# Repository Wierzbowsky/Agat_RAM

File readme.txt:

128kb RAM expansion for Agat computer v1.0. Created in 2016 by Wierzbowsky [RBSC].

Commercial usage is not allowed without the author's approval.

Contact: wierzbowsky@rbsc.su 

For more information see this forum's thread (in Russian): http://forum.agatcomp.ru//viewtopic.php?id=13

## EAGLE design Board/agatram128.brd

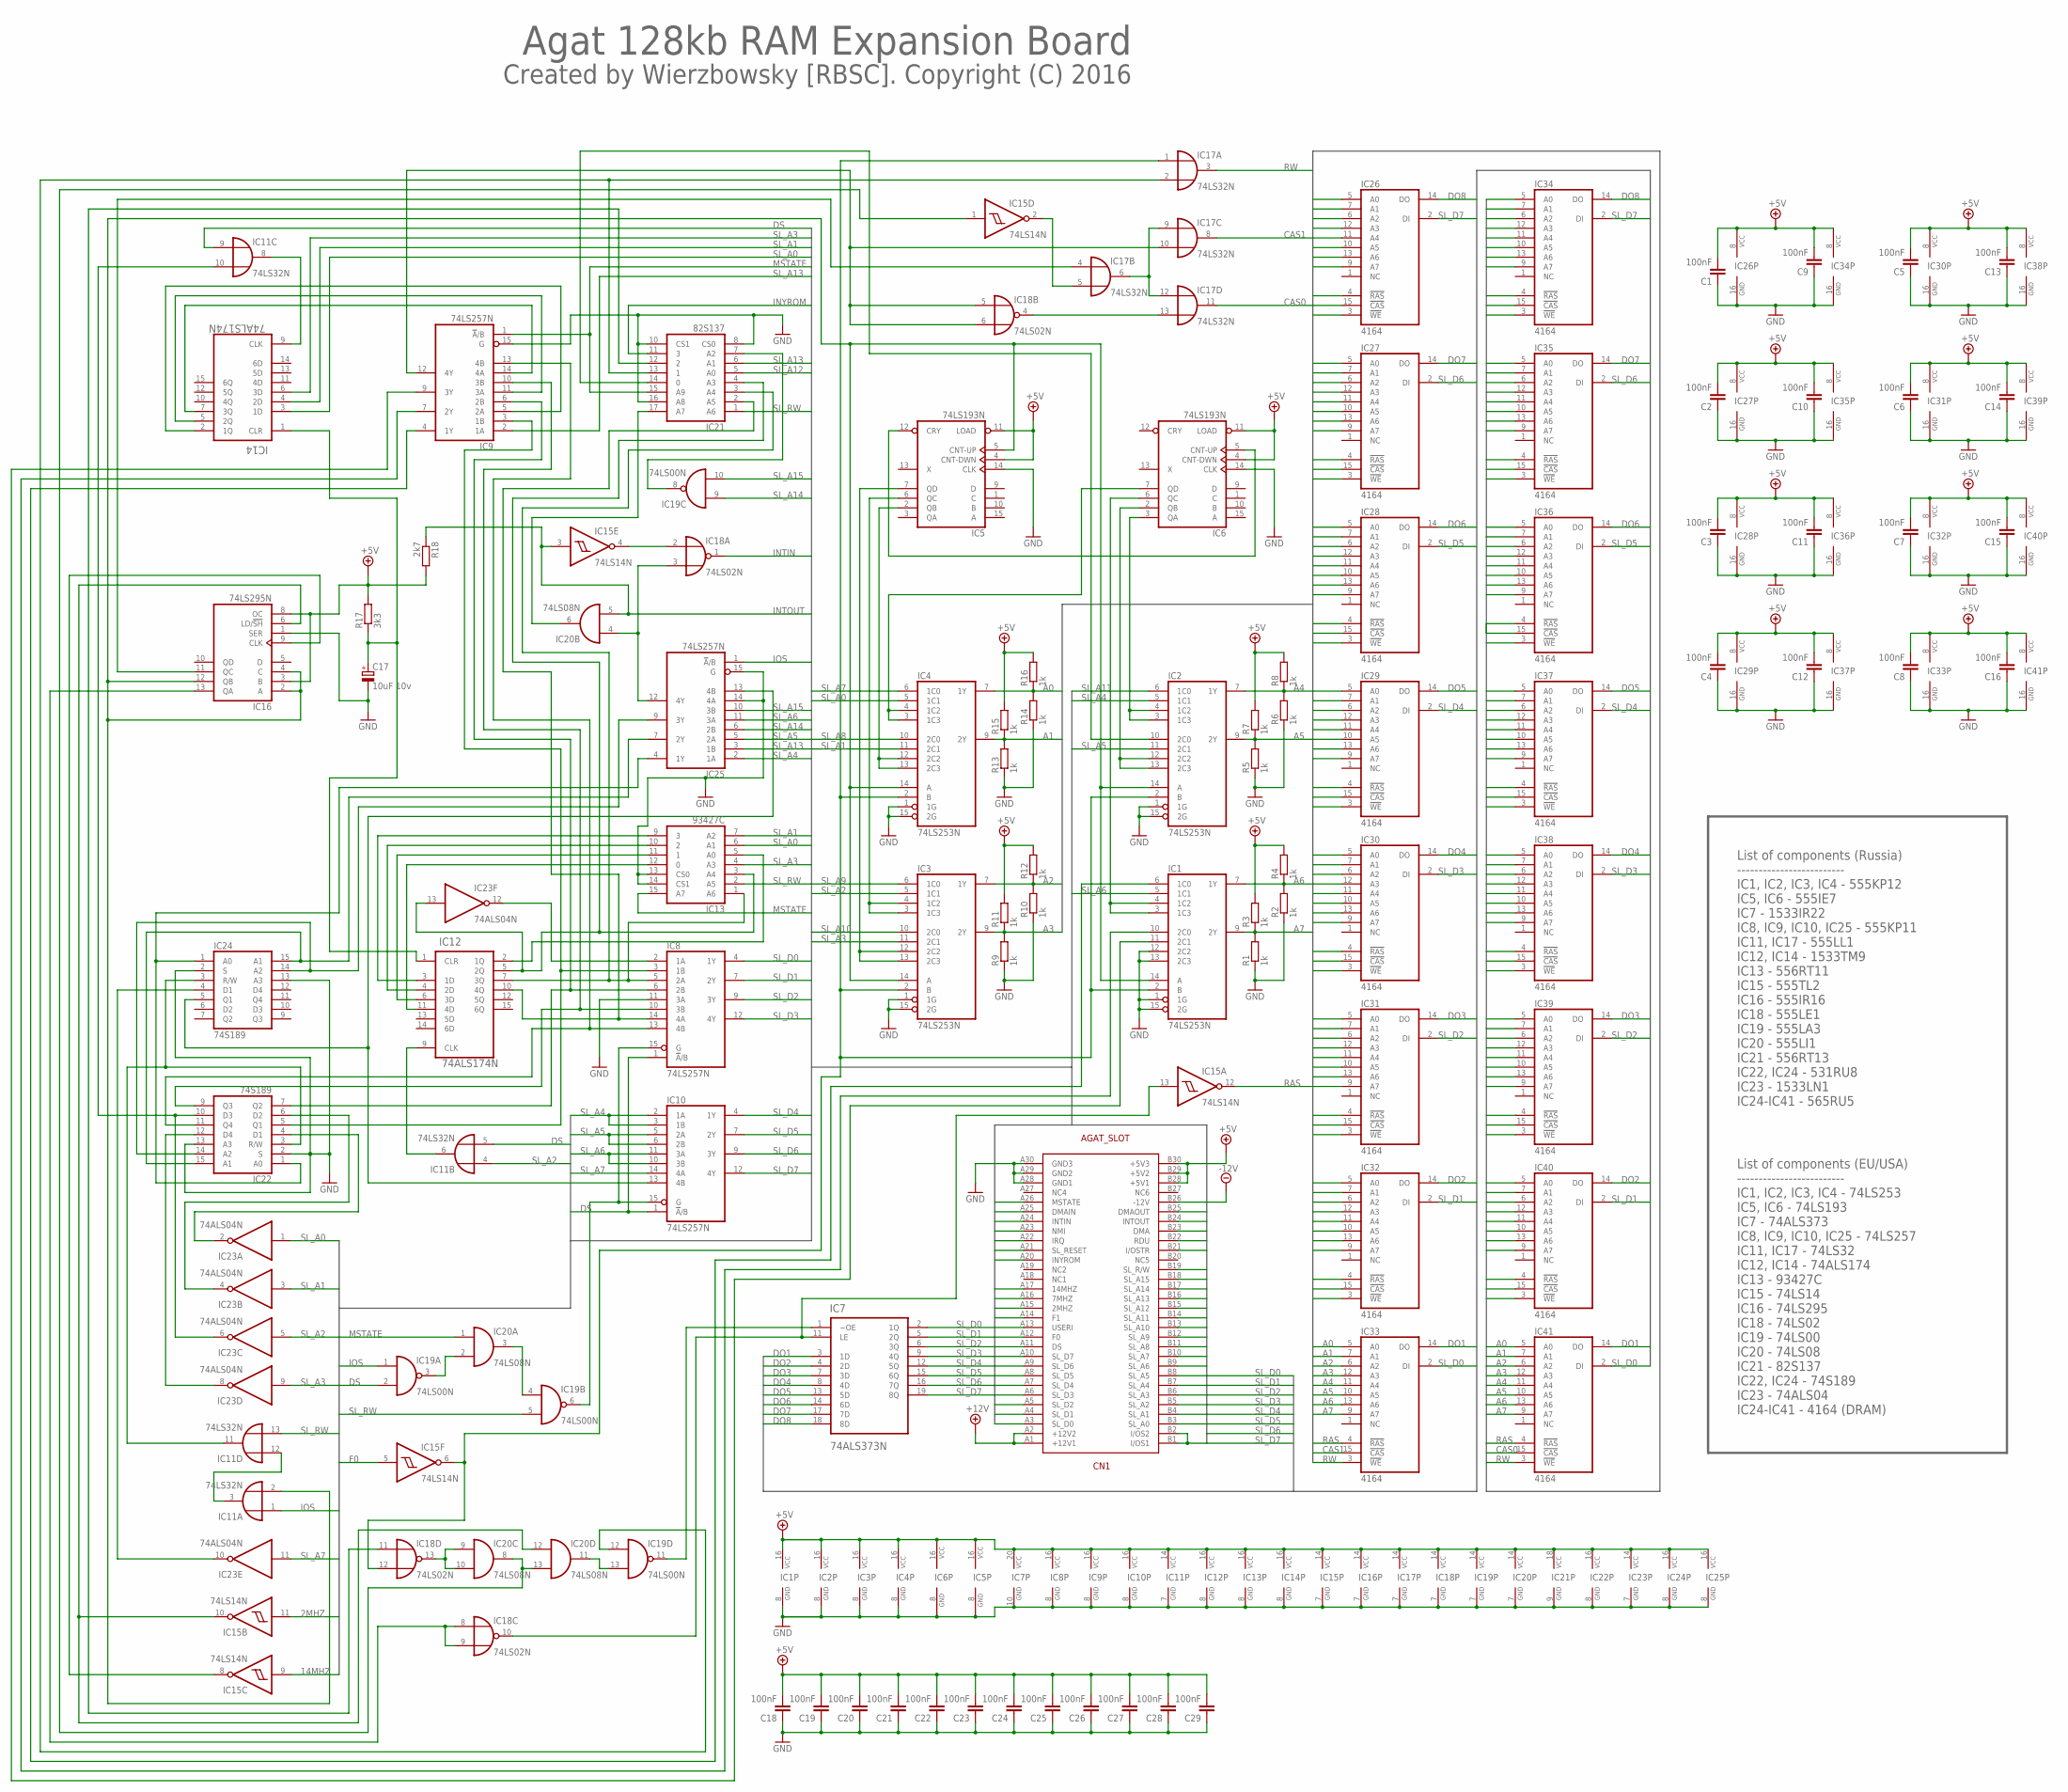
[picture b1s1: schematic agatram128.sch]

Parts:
C1, C2, C3, C4, C5, C6, C7, C8, C9, C10, C11, C12, C13, C14, C15, C16, C18, C19, C20, C21, C22, C23, C24, C25, C26, C27, C28, C29: 100nF; C050-025X075
C17: 10uF 10v; E15-5
CN1: AGAT_SLOT; AGAT_CONP
IC1, IC2, IC3, IC4: 74LS253N; DIL16
IC5, IC6: 74LS193N; DIL16
IC7: 74ALS373N; DIL20
IC8, IC9, IC10, IC25: 74LS257N; DIL16
IC11, IC17: 74LS32N; DIL14
IC12, IC14: 74ALS174N; DIL16
IC13: 93427C; DIL16
IC15: 74LS14N; DIL14
IC16: 74LS295N; DIL14
IC18: 74LS02N; DIL14
IC19: 74LS00N; DIL14
IC20: 74LS08N; DIL14
IC21: 82S137; DIL18
IC22, IC24: 74S189; DIL16
IC23: 74ALS04N; DIL14
IC26, IC27, IC28, IC29, IC30, IC31, IC32, IC33, IC34, IC35, IC36, IC37, IC38, IC39, IC40, IC41: 4164; DIL16
R1, R2, R3, R4, R5, R6, R7, R8, R9, R10, R11, R12, R13, R14, R15, R16: 1k; 0204/7
R17: 3k3; 0204/7
R18: 2k7; 0204/7

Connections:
2MHZ: CN1.A15 (2MHZ), IC15.11 (I)
7MHZ: CN1.A16 (7MHZ)
14MHZ: CN1.A17 (14MHZ), IC15.9 (I)
+5V: C1.2, C2.2, C3.2, C4.2, C5.2, C6.2, C7.2, C8.2, C9.2, C10.2, C11.2, C12.2, C13.2, C14.2, C15.2, C16.2, C18.2, C19.2, C20.2, C21.2, C22.2, C23.2, C24.2, C25.2, C26.2, C27.2, C28.2, C29.2, CN1.B28 (+5V1), CN1.B29 (+5V2), CN1.B30 (+5V3), IC1.16 (VCC), IC2.16 (VCC), IC3.16 (VCC), IC4.16 (VCC), IC5.4 (CNT-DWN), IC5.11 (LOAD), IC5.16 (VCC), IC6.4 (CNT-DWN), IC6.11 (LOAD), IC6.16 (VCC), IC7.20 (VCC), IC8.16 (VCC), IC9.16 (VCC), IC10.16 (VCC), IC11.14 (VCC), IC12.16 (VCC), IC13.16 (VCC), IC14.16 (VCC), IC15.14 (VCC), IC16.3 (B), IC16.8 (OC), IC16.14 (VCC), IC17.14 (VCC), IC18.14 (VCC), IC19.14 (VCC), IC20.14 (VCC), IC21.18 (VCC), IC22.16 (VCC), IC23.14 (VCC), IC24.16 (VCC), IC25.16 (VCC), IC26.8 (VCC), IC27.8 (VCC), IC28.8 (VCC), IC29.8 (VCC), IC30.8 (VCC), IC31.8 (VCC), IC32.8 (VCC), IC33.8 (VCC), IC34.8 (VCC), IC35.8 (VCC), IC36.8 (VCC), IC37.8 (VCC), IC38.8 (VCC), IC39.8 (VCC), IC40.8 (VCC), IC41.8 (VCC), R3.2, R4.2, R7.2, R8.2, R11.2, R12.2, R15.2, R16.2, R17.2, R18.2
+12V: CN1.A1 (+12V1), CN1.A2 (+12V2)
-12V: CN1.B26 (-12V)
A0: IC4.7 (1Y), IC26.5 (A0), IC27.5 (A0), IC28.5 (A0), IC29.5 (A0), IC30.5 (A0), IC31.5 (A0), IC32.5 (A0), IC33.5 (A0), IC34.5 (A0), IC35.5 (A0), IC36.5 (A0), IC37.5 (A0), IC38.5 (A0), IC39.5 (A0), IC40.5 (A0), IC41.5 (A0), R14.2, R16.1
A1: IC4.9 (2Y), IC26.7 (A1), IC27.7 (A1), IC28.7 (A1), IC29.7 (A1), IC30.7 (A1), IC31.7 (A1), IC32.7 (A1), IC33.7 (A1), IC34.7 (A1), IC35.7 (A1), IC36.7 (A1), IC37.7 (A1), IC38.7 (A1), IC39.7 (A1), IC40.7 (A1), IC41.7 (A1), R13.2, R15.1
A2: IC3.7 (1Y), IC26.6 (A2), IC27.6 (A2), IC28.6 (A2), IC29.6 (A2), IC30.6 (A2), IC31.6 (A2), IC32.6 (A2), IC33.6 (A2), IC34.6 (A2), IC35.6 (A2), IC36.6 (A2), IC37.6 (A2), IC38.6 (A2), IC39.6 (A2), IC40.6 (A2), IC41.6 (A2), R10.2, R12.1
A3: IC3.9 (2Y), IC26.12 (A3), IC27.12 (A3), IC28.12 (A3), IC29.12 (A3), IC30.12 (A3), IC31.12 (A3), IC32.12 (A3), IC33.12 (A3), IC34.12 (A3), IC35.12 (A3), IC36.12 (A3), IC37.12 (A3), IC38.12 (A3), IC39.12 (A3), IC40.12 (A3), IC41.12 (A3), R9.2, R11.1
A4: IC2.7 (1Y), IC26.11 (A4), IC27.11 (A4), IC28.11 (A4), IC29.11 (A4), IC30.11 (A4), IC31.11 (A4), IC32.11 (A4), IC33.11 (A4), IC34.11 (A4), IC35.11 (A4), IC36.11 (A4), IC37.11 (A4), IC38.11 (A4), IC39.11 (A4), IC40.11 (A4), IC41.11 (A4), R6.2, R8.1
A5: IC2.9 (2Y), IC26.10 (A5), IC27.10 (A5), IC28.10 (A5), IC29.10 (A5), IC30.10 (A5), IC31.10 (A5), IC32.10 (A5), IC33.10 (A5), IC34.10 (A5), IC35.10 (A5), IC36.10 (A5), IC37.10 (A5), IC38.10 (A5), IC39.10 (A5), IC40.10 (A5), IC41.10 (A5), R5.2, R7.1
A6: IC1.7 (1Y), IC26.13 (A6), IC27.13 (A6), IC28.13 (A6), IC29.13 (A6), IC30.13 (A6), IC31.13 (A6), IC32.13 (A6), IC33.13 (A6), IC34.13 (A6), IC35.13 (A6), IC36.13 (A6), IC37.13 (A6), IC38.13 (A6), IC39.13 (A6), IC40.13 (A6), IC41.13 (A6), R2.2, R4.1
A7: IC1.9 (2Y), IC26.9 (A7), IC27.9 (A7), IC28.9 (A7), IC29.9 (A7), IC30.9 (A7), IC31.9 (A7), IC32.9 (A7), IC33.9 (A7), IC34.9 (A7), IC35.9 (A7), IC36.9 (A7), IC37.9 (A7), IC38.9 (A7), IC39.9 (A7), IC40.9 (A7), IC41.9 (A7), R1.2, R3.1
CAS0: IC17.11 (O), IC34.15 (!CAS), IC35.15 (!CAS), IC36.15 (!CAS), IC37.15 (!CAS), IC38.15 (!CAS), IC39.15 (!CAS), IC40.15 (!CAS), IC41.15 (!CAS)
CAS1: IC17.8 (O), IC26.15 (!CAS), IC27.15 (!CAS), IC28.15 (!CAS), IC29.15 (!CAS), IC30.15 (!CAS), IC31.15 (!CAS), IC32.15 (!CAS), IC33.15 (!CAS)
DMA: CN1.B23 (DMA)
DMAIN: CN1.A25 (DMAIN)
DMAOUT: CN1.B25 (DMAOUT)
DO1: IC7.3 (1D), IC33.14 (DO), IC41.14 (DO)
DO2: IC7.4 (2D), IC32.14 (DO), IC40.14 (DO)
DO3: IC7.7 (3D), IC31.14 (DO), IC39.14 (DO)
DO4: IC7.8 (4D), IC30.14 (DO), IC38.14 (DO)
DO5: IC7.13 (5D), IC29.14 (DO), IC37.14 (DO)
DO6: IC7.14 (6D), IC28.14 (DO), IC36.14 (DO)
DO7: IC7.17 (7D), IC27.14 (DO), IC35.14 (DO)
DO8: IC7.18 (8D), IC26.14 (DO), IC34.14 (DO)
DS: CN1.A11 (DS), IC8.1 (!A!/B), IC10.1 (!A!/B), IC11.5 (I1), IC11.9 (I0), IC19.2 (I1)
F0: CN1.A12 (F0), IC15.5 (I)
F1: CN1.A14 (F1)
GND: C1.1, C2.1, C3.1, C4.1, C5.1, C6.1, C7.1, C8.1, C9.1, C10.1, C11.1, C12.1, C13.1, C14.1, C15.1, C16.1, C17.-, C18.1, C19.1, C20.1, C21.1, C22.1, C23.1, C24.1, C25.1, C26.1, C27.1, C28.1, C29.1, CN1.A28 (GND1), CN1.A29 (GND2), CN1.A30 (GND3), IC1.1 (1G), IC1.8 (GND), IC1.12 (2C2), IC1.13 (2C3), IC1.15 (2G), IC2.1 (1G), IC2.8 (GND), IC2.15 (2G), IC3.1 (1G), IC3.8 (GND), IC3.15 (2G), IC4.1 (1G), IC4.8 (GND), IC4.15 (2G), IC5.8 (GND), IC5.14 (CLK), IC6.8 (GND), IC6.14 (CLK), IC7.10 (GND), IC8.8 (GND), IC8.11 (3A), IC9.8 (GND), IC9.15 (G), IC10.8 (GND), IC11.7 (GND), IC12.8 (GND), IC13.8 (GND), IC13.13 (CS0), IC13.14 (CS1), IC14.8 (GND), IC15.7 (GND), IC16.1 (SER), IC16.7 (GND), IC17.7 (GND), IC18.7 (GND), IC19.7 (GND), IC20.7 (GND), IC21.8 (CS0), IC21.9 (GND), IC21.10 (CS1), IC21.16 (A8), IC22.2 (S), IC22.8 (GND), IC22.13 (A3), IC23.7 (GND), IC24.2 (S), IC24.8 (GND), IC24.13 (A3), IC25.8 (GND), IC25.14 (4A), IC25.15 (G), IC26.16 (GND), IC27.16 (GND), IC28.16 (GND), IC29.16 (GND), IC30.16 (GND), IC31.16 (GND), IC32.16 (GND), IC33.16 (GND), IC34.16 (GND), IC35.16 (GND), IC36.16 (GND), IC37.16 (GND), IC38.16 (GND), IC39.16 (GND), IC40.16 (GND), IC41.16 (GND), R1.1, R2.1, R5.1, R6.1, R9.1, R10.1, R13.1, R14.1
INTIN: CN1.A24 (INTIN), IC18.1 (O)
INTOUT: CN1.B24 (INTOUT), IC15.3 (I), IC20.5 (I1), R18.1
INYROM: CN1.A20 (INYROM), IC21.11 (3)
IOS: CN1.B1 (I/OS1), CN1.B2 (I/OS2), IC11.1 (I0), IC19.1 (I0), IC25.1 (!A!/B)
IOSTR: CN1.B21 (I/OSTR)
IRQ: CN1.A22 (IRQ)
MSTATE: CN1.A26 (MSTATE), IC9.1 (!A!/B), IC13.15 (A7), IC20.1 (I0), IC21.15 (A9)
unnamed: IC17.6 (O), IC17.9 (I0), IC17.12 (I0)
unnamed: IC7.1 (~OE), IC19.11 (O)
unnamed: IC7.11 (LE), IC15.13 (I), IC18.10 (O)
unnamed: IC19.8 (O), IC21.7 (A2)
unnamed: IC8.15 (G), IC10.15 (G), IC19.6 (O)
unnamed: IC11.6 (O), IC12.9 (CLK)
unnamed: IC12.2 (1Q), IC13.5 (A0)
unnamed: IC12.5 (2Q), IC13.3 (A4), IC21.4 (A3), IC23.13 (I)
unnamed: IC8.5 (2A), IC12.7 (3Q), IC13.1 (A6), IC21.3 (A4)
unnamed: IC12.6 (3D), IC13.11 (1)
unnamed: IC8.14 (4A), IC12.10 (4Q), IC21.2 (A5)
unnamed: IC12.11 (4D), IC13.12 (0)
unnamed: IC12.4 (2D), IC13.10 (2)
unnamed: IC12.3 (1D), IC13.9 (3)
unnamed: IC9.14 (4A), IC14.7 (3Q)
unnamed: IC8.2 (1A), IC23.12 (O)
unnamed: IC9.11 (3A), IC14.5 (2Q)
unnamed: IC9.5 (2A), IC14.2 (1Q)
unnamed: IC2.10 (2C0), IC21.14 (0)
unnamed: IC22.4 (D1), IC23.2 (O)
unnamed: IC22.6 (D2), IC23.4 (O)
unnamed: IC11.10 (I1), IC22.10 (D3), IC23.6 (O)
unnamed: IC22.12 (D4), IC23.8 (O)
unnamed: IC22.14 (A2), IC24.14 (A2), IC25.9 (3Y)
unnamed: IC11.11 (O), IC22.3 (R/W), IC24.3 (R/W)
unnamed: IC18.3 (I1), IC20.4 (I0), IC25.12 (4Y)
unnamed: IC11.8 (O), IC14.9 (CLK)
unnamed: IC11.3 (O), IC11.12 (I0)
unnamed: IC23.10 (O), IC24.4 (D1)
unnamed: IC19.4 (I0), IC20.3 (O)
unnamed: IC19.3 (O), IC20.2 (I1)
unnamed: IC22.1 (A0), IC24.1 (A0), IC25.4 (1Y)
unnamed: IC10.13 (4B), IC24.5 (Q1), IC25.13 (4B)
unnamed: IC22.15 (A1), IC24.15 (A1), IC25.7 (2Y)
unnamed: IC15.2 (O), IC17.5 (I1)
unnamed: IC4.12 (2C2), IC4.13 (2C3), IC5.2 (QB)
unnamed: IC3.3 (1C3), IC3.4 (1C2), IC5.6 (QC)
unnamed: IC3.12 (2C2), IC3.13 (2C3), IC5.7 (QD)
unnamed: IC5.12 (CRY), IC6.5 (CNT-UP)
unnamed: IC2.3 (1C3), IC2.4 (1C2), IC6.3 (QA)
unnamed: IC2.12 (2C2), IC2.13 (2C3), IC6.2 (QB)
unnamed: IC1.3 (1C3), IC1.4 (1C2), IC6.6 (QC)
unnamed: IC4.3 (1C3), IC4.4 (1C2), IC6.7 (QD)
unnamed: IC1.2 (B), IC2.2 (B), IC3.2 (B), IC4.2 (B), IC15.6 (O), IC17.1 (I0), IC18.12 (I1)
unnamed: IC18.13 (O), IC20.9 (I0), IC20.10 (I1)
unnamed: IC18.11 (I0), IC21.12 (2)
unnamed: IC15.1 (I), IC20.8 (O), IC20.13 (I1)
unnamed: IC19.13 (I1), IC20.11 (O)
unnamed: IC15.10 (O), IC16.6 (LD/!SH), IC20.12 (I0)
unnamed: IC15.8 (O), IC16.9 (CLK)
unnamed: IC1.14 (A), IC2.14 (A), IC3.14 (A), IC4.14 (A), IC5.5 (CNT-UP), IC11.2 (I1), IC16.2 (A), IC16.4 (C), IC16.12 (QB)
unnamed: IC16.11 (QC), IC17.4 (I0)
unnamed: IC17.2 (I1), IC19.12 (I0), IC21.13 (1)
unnamed: IC16.13 (QA), IC18.8 (I0), IC18.9 (I1)
unnamed: IC15.4 (O), IC18.2 (I0)
unnamed: IC20.6 (O), IC21.17 (A7)
unnamed: IC17.13 (I1), IC18.4 (O)
unnamed: IC9.12 (4Y), IC17.10 (I1), IC18.5 (I0), IC18.6 (I1)
unnamed: IC1.6 (1C0), IC9.4 (1Y)
unnamed: IC1.10 (2C0), IC9.7 (2Y)
unnamed: IC1.11 (2C1), IC9.9 (3Y)
unnamed: IC8.3 (1B), IC9.3 (1B), IC22.5 (Q1)
unnamed: IC8.6 (2B), IC9.6 (2B), IC22.7 (Q2)
unnamed: IC8.10 (3B), IC9.10 (3B), IC22.9 (Q3)
unnamed: IC8.13 (4B), IC9.13 (4B), IC22.11 (Q4)
NMI: CN1.A23 (NMI)
RAS: IC15.12 (O), IC26.4 (!RAS), IC27.4 (!RAS), IC28.4 (!RAS), IC29.4 (!RAS), IC30.4 (!RAS), IC31.4 (!RAS), IC32.4 (!RAS), IC33.4 (!RAS), IC34.4 (!RAS), IC35.4 (!RAS), IC36.4 (!RAS), IC37.4 (!RAS), IC38.4 (!RAS), IC39.4 (!RAS), IC40.4 (!RAS), IC41.4 (!RAS)
RDU: CN1.B22 (RDU)
RES: C17.+, IC12.1 (CLR), IC14.1 (CLR), R17.1
RW: IC17.3 (O), IC26.3 (!WE), IC27.3 (!WE), IC28.3 (!WE), IC29.3 (!WE), IC30.3 (!WE), IC31.3 (!WE), IC32.3 (!WE), IC33.3 (!WE), IC34.3 (!WE), IC35.3 (!WE), IC36.3 (!WE), IC37.3 (!WE), IC38.3 (!WE), IC39.3 (!WE), IC40.3 (!WE), IC41.3 (!WE)
SL_A0: CN1.B3 (SL_A0), IC4.5 (1C1), IC13.6 (A1), IC14.3 (1D), IC23.1 (I)
SL_A1: CN1.B4 (SL_A1), IC4.11 (2C1), IC13.7 (A2), IC14.4 (2D), IC23.3 (I)
SL_A2: CN1.B5 (SL_A2), IC3.5 (1C1), IC11.4 (I0), IC23.5 (I)
SL_A3: CN1.B6 (SL_A3), IC3.11 (2C1), IC13.4 (A3), IC14.6 (3D), IC23.9 (I)
SL_A4: CN1.B7 (SL_A4), IC2.5 (1C1), IC10.2 (1A), IC10.3 (1B), IC25.2 (1A)
SL_A5: CN1.B8 (SL_A5), IC2.11 (2C1), IC10.5 (2A), IC10.6 (2B), IC25.5 (2A)
SL_A6: CN1.B9 (SL_A6), IC1.5 (1C1), IC10.10 (3B), IC10.11 (3A), IC25.11 (3A)
SL_A7: CN1.B10 (SL_A7), IC4.6 (1C0), IC10.14 (4A), IC23.11 (I)
SL_A8: CN1.B11 (SL_A8), IC4.10 (2C0)
SL_A9: CN1.B12 (SL_A9), IC3.6 (1C0)
SL_A10: CN1.B13 (SL_A10), IC3.10 (2C0)
SL_A11: CN1.B14 (SL_A11), IC2.6 (1C0)
SL_A12: CN1.B15 (SL_A12), IC21.5 (A0)
SL_A13: CN1.B16 (SL_A13), IC9.2 (1A), IC21.6 (A1), IC25.3 (1B)
SL_A14: CN1.B17 (SL_A14), IC19.9 (I0), IC25.6 (2B)
SL_A15: CN1.B18 (SL_A15), IC19.10 (I1), IC25.10 (3B)
SL_D0: CN1.A3 (SL_D0), IC7.2 (1Q), IC8.4 (1Y), IC33.2 (DI), IC41.2 (DI)
SL_D1: CN1.A4 (SL_D1), IC7.5 (2Q), IC8.7 (2Y), IC32.2 (DI), IC40.2 (DI)
SL_D2: CN1.A5 (SL_D2), IC7.6 (3Q), IC8.9 (3Y), IC31.2 (DI), IC39.2 (DI)
SL_D3: CN1.A6 (SL_D3), IC7.9 (4Q), IC8.12 (4Y), IC30.2 (DI), IC38.2 (DI)
SL_D4: CN1.A7 (SL_D4), IC7.12 (5Q), IC10.4 (1Y), IC29.2 (DI), IC37.2 (DI)
SL_D5: CN1.A8 (SL_D5), IC7.15 (6Q), IC10.7 (2Y), IC28.2 (DI), IC36.2 (DI)
SL_D6: CN1.A9 (SL_D6), IC7.16 (7Q), IC10.9 (3Y), IC27.2 (DI), IC35.2 (DI)
SL_D7: CN1.A10 (SL_D7), IC7.19 (8Q), IC10.12 (4Y), IC26.2 (DI), IC34.2 (DI)
SL_RESET: CN1.A21 (SL_RESET)
SL_RW: CN1.B19 (SL_R/W), IC11.13 (I1), IC13.2 (A5), IC19.5 (I1), IC21.1 (A6)
USERI: CN1.A13 (USERI)

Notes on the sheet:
Agat 128kb RAM Expansion Board
List of components (Russia) ------------------------- IC1, IC2, IC3, IC4 - 555KP12 IC5, IC6 - 555IE7 IC7 - 1533IR22 IC8, IC9, IC10, IC25 - 555KP11 IC11, IC17 - 555LL1 IC12, IC14 - 1533TM9 IC13 - 556RT11 IC15 - 555TL2 IC16 - 555IR16 IC18 - 555LE1 IC19 - 555LA3 IC20 - 555LI1 IC21 - 556RT13 IC22, IC24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
List of components (EU/USA) ------------------------- IC1, IC2, IC3, IC4 - 74LS253 IC5, IC6 - 74LS193 IC7 - 74ALS373 IC8, IC9, IC10, IC25 - 74LS257 IC11, IC17 - 74LS32 IC12, IC14 - 74ALS174 IC13 - 93427C IC15 - 74LS14 IC16 - 74LS295 IC18 - 74LS02 IC19 - 74LS00 IC20 - 74LS08 IC21 - 82S137 IC22, IC24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
Created by Wierzbowsky [RBSC]. Copyright (C) 2016

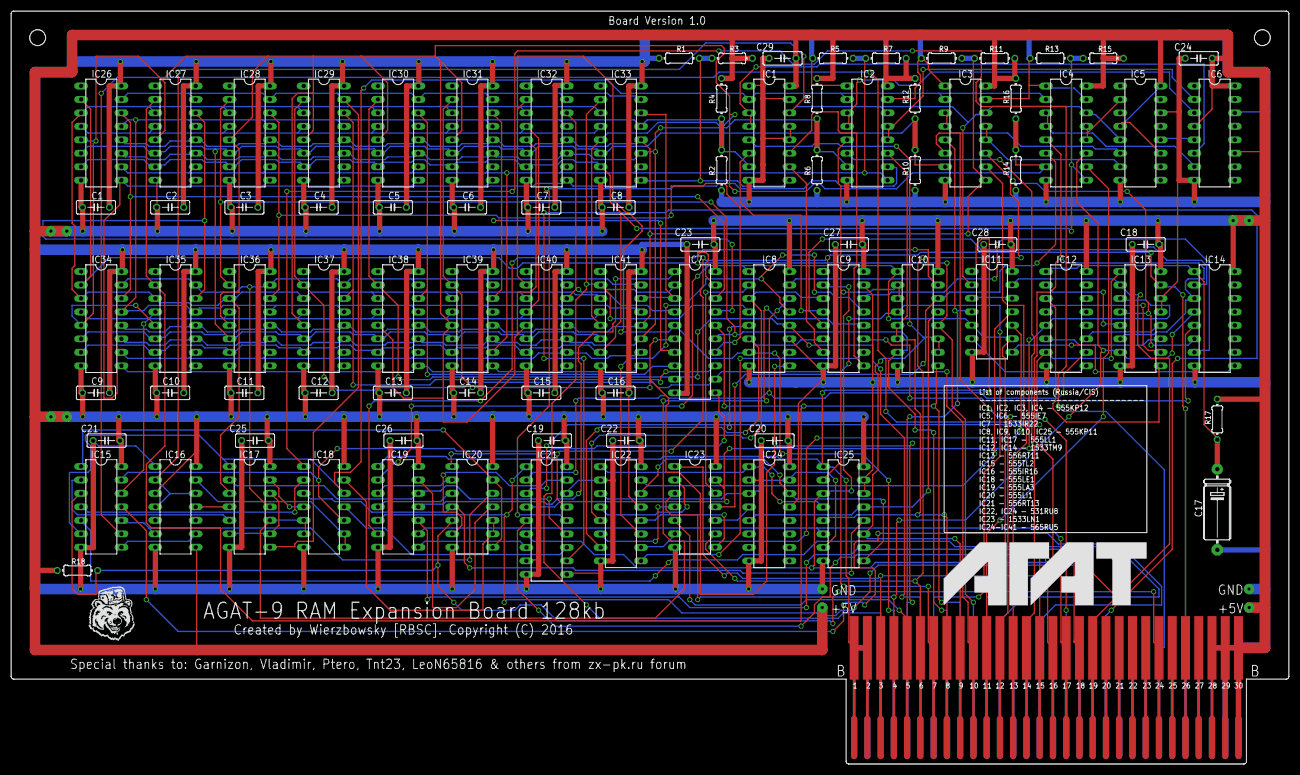
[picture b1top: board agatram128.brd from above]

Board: 2 copper layers, 241.0 x 142.0 mm, 89 parts (0 on the bottom side), 123 nets.

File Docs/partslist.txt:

Partlist

Assembly variant: 

Part     Value          Package      Library             Position (mm)         Orientation

C1       100nF          C050-025X075 rcl                 (-225 89)             R180
C2       100nF          C050-025X075 rcl                 (-211 89)             R180
C3       100nF          C050-025X075 rcl                 (-197 89)             R180
C4       100nF          C050-025X075 rcl                 (-183 89)             R180
C5       100nF          C050-025X075 rcl                 (-169 89)             R180
C6       100nF          C050-025X075 rcl                 (-155 89)             R180
C7       100nF          C050-025X075 rcl                 (-141 89)             R180
C8       100nF          C050-025X075 rcl                 (-127 89)             R180
C9       100nF          C050-025X075 rcl                 (-225 54)             R180
C10      100nF          C050-025X075 rcl                 (-211 54)             R180
C11      100nF          C050-025X075 rcl                 (-197 54)             R180
C12      100nF          C050-025X075 rcl                 (-183 54)             R180
C13      100nF          C050-025X075 rcl                 (-169 54)             R180
C14      100nF          C050-025X075 rcl                 (-155 54)             R180
C15      100nF          C050-025X075 rcl                 (-141 54)             R180
C16      100nF          C050-025X075 rcl                 (-127 54)             R180
C17      10uF 10v       E15-5        rcl                 (-13.5 32)            R270
C18      100nF          C050-025X075 rcl                 (-27 82)              R0
C19      100nF          C050-025X075 rcl                 (-139 45)             R0
C20      100nF          C050-025X075 rcl                 (-97 45)              R0
C21      100nF          C050-025X075 rcl                 (-223 45)             R0
C22      100nF          C050-025X075 rcl                 (-125 45)             R0
C23      100nF          C050-025X075 rcl                 (-111 82)             R0
C24      100nF          C050-025X075 rcl                 (-17 117.1)           R0
C25      100nF          C050-025X075 rcl                 (-195 45)             R0
C26      100nF          C050-025X075 rcl                 (-167 45)             R0
C27      100nF          C050-025X075 rcl                 (-83 82)              R0
C28      100nF          C050-025X075 rcl                 (-55 82)              R0
C29      100nF          C050-025X075 rcl                 (-95.5 117.1)         R0
CN1      AGAT_SLOT      AGAT_CONP    AGAT_Slot_Connector (-7 -16)              R0
IC1      74LS253N       DIL16        74xx-eu             (-98 103)             R270
IC2      74LS253N       DIL16        74xx-eu             (-79.5 103)           R270
IC3      74LS253N       DIL16        74xx-eu             (-61 103)             R270
IC4      74LS253N       DIL16        74xx-eu             (-42 103)             R270
IC5      74LS193N       DIL16        0RB_TTL             (-28 103)             R270
IC6      74LS193N       DIL16        0RB_TTL             (-14 103)             R270
IC7      74ALS373N      DIL20        74ALS373            (-112 68)             R270
IC8      74LS257N       DIL16        74xx-eu             (-98 68)              R270
IC9      74LS257N       DIL16        74xx-eu             (-84 68)              R270
IC10     74LS257N       DIL16        74xx-eu             (-70 68)              R270
IC11     74LS32N        DIL14        74xx-eu             (-56 69.3)            R270
IC12     74ALS174N      DIL16        74ALS174            (-42 68)              R270
IC13     93427C         DIL16        93427C              (-28 68)              R270
IC14     74ALS174N      DIL16        74ALS174            (-14 68)              R270
IC15     74LS14N        DIL14        74xx-eu             (-224 32.5)           R270
IC16     74LS295N       DIL14        74LS295             (-210 32.5)           R270
IC17     74LS32N        DIL14        74xx-eu             (-196 32.5)           R270
IC18     74LS02N        DIL14        74xx-eu             (-182 32.5)           R270
IC19     74LS00N        DIL14        74xx-eu             (-168 32.5)           R270
IC20     74LS08N        DIL14        74xx-eu             (-154 32.5)           R270
IC21     82S137         DIL18        82S137              (-140 31.2)           R270
IC22     74S189         DIL16        74S189              (-126 31.2)           R270
IC23     74ALS04N       DIL14        74xx-eu             (-112 32.5)           R270
IC24     74S189         DIL16        74S189              (-98 31.2)            R270
IC25     74LS257N       DIL16        74xx-eu             (-84 31.2)            R270
IC26     4164           DIL16        0RB_Memory          (-224 103)            R270
IC27     4164           DIL16        0RB_Memory          (-210 103)            R270
IC28     4164           DIL16        0RB_Memory          (-196 103)            R270
IC29     4164           DIL16        0RB_Memory          (-182 103)            R270
IC30     4164           DIL16        0RB_Memory          (-168 103)            R270
IC31     4164           DIL16        0RB_Memory          (-154 103)            R270
IC32     4164           DIL16        0RB_Memory          (-140 103)            R270
IC33     4164           DIL16        0RB_Memory          (-126 103)            R270
IC34     4164           DIL16        0RB_Memory          (-224 68)             R270
IC35     4164           DIL16        0RB_Memory          (-210 68)             R270
IC36     4164           DIL16        0RB_Memory          (-196 68)             R270
IC37     4164           DIL16        0RB_Memory          (-182 68)             R270
IC38     4164           DIL16        0RB_Memory          (-168 68)             R270
IC39     4164           DIL16        0RB_Memory          (-154 68)             R270
IC40     4164           DIL16        0RB_Memory          (-140 68)             R270
IC41     4164           DIL16        0RB_Memory          (-126 68)             R270
R1       1k             0204/7       rcl                 (-115 117.1)          R0
R2       1k             0204/7       rcl                 (-107 96)             R90
R3       1k             0204/7       rcl                 (-105 117.1)          R0
R4       1k             0204/7       rcl                 (-107 109.5)          R90
R5       1k             0204/7       rcl                 (-86 117.1)           R0
R6       1k             0204/7       rcl                 (-89 96)              R90
R7       1k             0204/7       rcl                 (-76 117.1)           R0
R8       1k             0204/7       rcl                 (-89 109.5)           R90
R9       1k             0204/7       rcl                 (-65.5 117.1)         R0
R10      1k             0204/7       rcl                 (-70.5 96)            R90
R11      1k             0204/7       rcl                 (-55.5 117.1)         R0
R12      1k             0204/7       rcl                 (-70.5 109.5)         R90
R13      1k             0204/7       rcl                 (-45 117.1)           R0
R14      1k             0204/7       rcl                 (-51.5 96)            R90
R15      1k             0204/7       rcl                 (-35 117.1)           R0
R16      1k             0204/7       rcl                 (-51.5 109.5)         R90
R17      3k3            0204/7       rcl                 (-13.5 49)            R90
R18      2k7            0204/7       rcl                 (-228.5 20.5)         R180

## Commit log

2023-07-23 :confetti_ball: Added .gitattributes & .gitignore files
2023-07-23 Release 23.07.2023
    Files from 2016 have been added into the repository
